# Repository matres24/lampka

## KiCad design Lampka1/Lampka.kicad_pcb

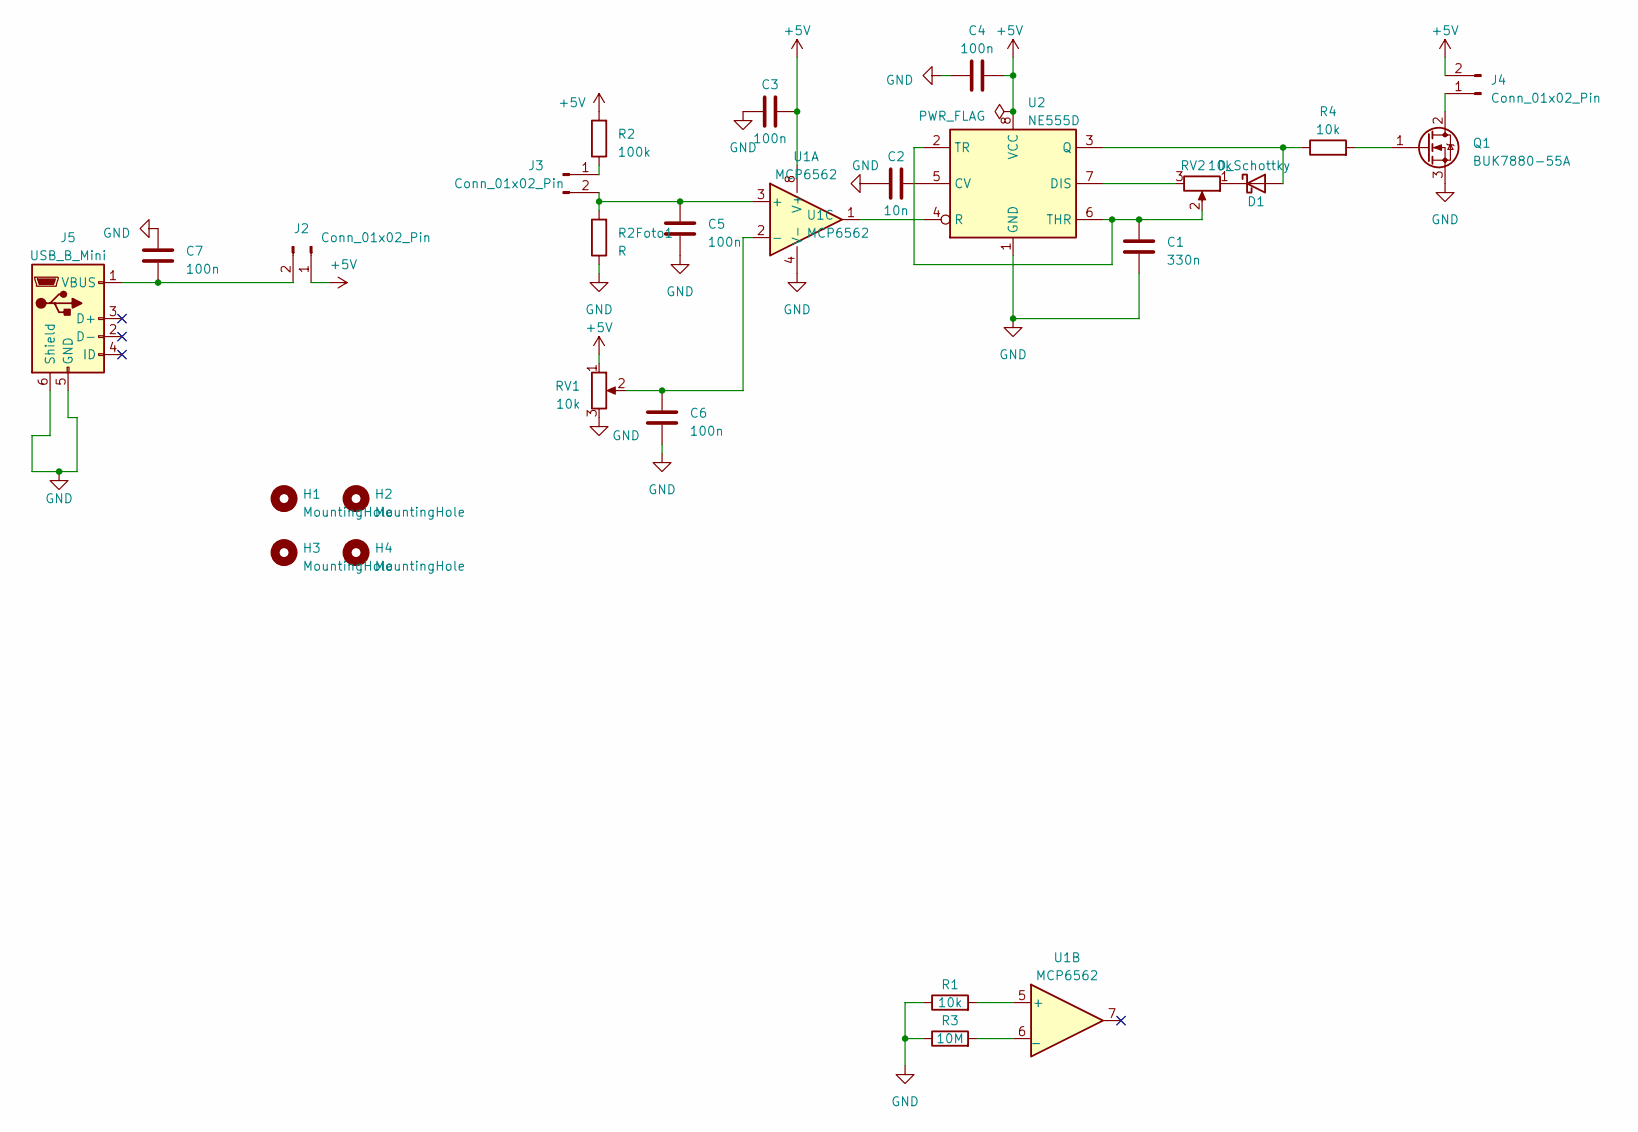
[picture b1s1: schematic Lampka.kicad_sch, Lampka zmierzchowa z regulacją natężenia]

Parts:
C1: 330n; C_0805_2012Metric
C2: 10n; C_0805_2012Metric
C3, C4, C5, C6, C7: 100n; C_0805_2012Metric
D1: D_Schottky; D_SOD-123F
H1, H2, H3, H4: MountingHole; MountingHole_2.2mm_M2_ISO14580
J2, J3, J4: Conn_01x02_Pin; PinHeader_1x02_P2.54mm_Vertical
J5: USB_B_Mini; USB_Mini-B_Wuerth_65100516121_Horizontal
Q1: BUK7880-55A; SOT-223-3_TabPin2
R1, R4: 10k; R_0805_2012Metric_Pad1.20x1.40mm_HandSolder
R2: 100k; R_0805_2012Metric_Pad1.20x1.40mm_HandSolder
R2Foto1: R; PinHeader_1x02_P2.54mm_Vertical
R3: 10M; R_0805_2012Metric_Pad1.20x1.40mm_HandSolder
RV1, RV2: 10k; PinHeader_1x03_P2.54mm_Vertical
U1: MCP6562; SO-8_3.9x4.9mm_P1.27mm
U2: NE555D; SOIC-8_3.9x4.9mm_P1.27mm

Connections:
+5V: C3.2, C4.2, J2.1, J4.2, R2.2, RV1.1, U1.8 (V+), U2.8 (VCC)
GND: C1.2, C2.1, C3.1, C4.1, C5.2, C6.2, C7.2, J5.5 (GND), J5.6 (Shield), Q1.3 (S), R1.1, R2Foto1.1, R3.1, RV1.3, U1.4 (V-), U2.1 (GND); also elsewhere on the board
unnamed: D1.2 (A), R4.1, U2.3 (Q)
unnamed: D1.1 (K), RV2.1
unnamed: C7.1, J2.2, J5.1 (VBUS)
unnamed: J3.1, R2.1
unnamed 6: C5.1, J3.2, R2Foto1.2, U1.3 (+); also elsewhere on the board
unnamed: J4.1, Q1.2 (D)
unnamed: Q1.1 (G), R4.2
unnamed: C6.1, RV1.2, U1.2 (-)
unnamed: R1.2, U1.5 (+)
unnamed: R3.2, U1.6 (_)
unnamed: C2.2, U2.5 (CV)
unnamed: RV2.3, U2.7 (DIS)
unnamed: U1.1, U2.4 (R)
unnamed: C1.1, RV2.2, U2.2 (TR), U2.6 (THR)

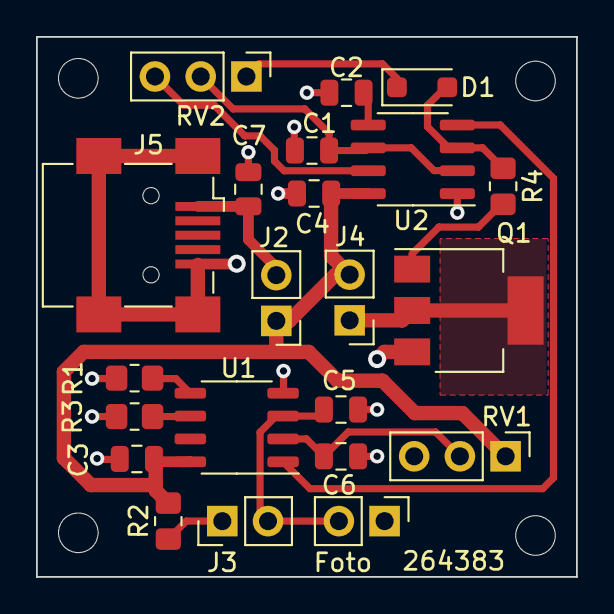
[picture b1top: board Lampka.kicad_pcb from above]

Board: 2 copper layers, 30.0 x 30.0 mm, 26 parts (0 on the bottom side), 16 nets.

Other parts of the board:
Foto: R; PinHeader_1x02_P2.54mm_Vertical

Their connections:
GND: Foto.1; also elsewhere on the board
unnamed 6: Foto.2; also elsewhere on the board
